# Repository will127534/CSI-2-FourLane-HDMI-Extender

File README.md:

# CSI-2-FourLane-HDMI-Extender
A simple MIPI CSI-2 extender with 4-lane support through HDMI cable

## Hardware
Technically, this isn’t supposed to work, but it kind of does. It relies on HDMI cables with Ethernet support to provide the fifth differential pair needed to transmit 4-lane MIPI signals through the HDMI cable.

The board is very simple. The receiver can either use the 3.3V from the FPC cable or an external power input to supply the HDMI connector’s power output. The HDMI connector location matches the USB connector on the Raspberry Pi 5 to simplify case design.

The transmitter board has a DC-DC step-down converter with a 3.3V output and a bypass option to power camera boards. For the StarlightEye (which needs a 5V input), there is also a connector that taps into the HDMI power input to supply power—this could also power something else, like an LED light source. Additionally, there is a QWIIC connector for sideband communication. Finally, the board’s form factor includes a cutout for the OneInchEye 2.0.

## Notes

This project came about because GMSL2 was too difficult to implement, and I needed something to extend my 4-lane MIPI cameras. If you’re reading this, you probably already know there are a few HDMI extender boards for MIPI cameras out there. However, most only support 2-lane MIPI, while I specifically needed 4-lane MIPI.

Where’s the catch? The standard HDMI cable only has four high-speed differential pairs, so that’s typically not enough for 4-lane MIPI (which requires 4 data pairs + 1 clock pair). However, HDMI includes an extension standard that reuses the HPD and UTILITY pins on the connector for a fifth differential pair called HEAC. This pair is meant for a bi-directional higher-speed sideband signal for Ethernet or Audio. Spec-wise, it doesn't have to carry signals as high-speed as the main video data. However, from a manufacturing standpoint, it’s often just as capable, because many manufacturers use the same type of differential pair cable for the fifth pair. (See [this teardown video by ChargerLab ](https://www.youtube.com/watch?v=UTeQvG3jk0k) as an example.)

For testing, I used the Cable Matters 2-Pack Ultra Thin HDMI Cable series; the 6-ft version is the maximum length that can run both the OneInchEye and StarlightEye at 1440 Mbps/lane with 4-lane MIPI.

Note: If you are using my IMX585 driver, you must lower the link speed from 1782 Mbps/lane to 1440 Mbps/lane by changing [this](https://github.com/will127534/imx585-v4l2-driver/blob/main/imx585.c#L210) line to 0x03.

Lastly, I did try using MIPI redrivers and retimers from [Ti](https://www.ti.com/product/SN65DPHY440SS) and [Diodes](https://www.diodes.com/part/view/PI2MEQX2505). The receiver board was originally designed with an active redriver/retimer (both parts are conveniently pin-to-pin compatible). However, due to the board’s pin layout, the differential pairs would need a polarity swap, and TI’s retimer wouldn’t work, even with [this register](https://e2e.ti.com/support/interface-group/interface/f/interface-forum/1187578/sn65dphy440ss-in-a-csi-application-is-it-possible-to-invert-n-and-p-on-both-sides-of-the-chip-except-for-the-clk) configured. As for the redriver, for some reason I couldn’t get it to work well with a 6-ft cable—only with a very short HDMI cable. The redriver is polarity-invariant, but even after playing around with the different tuning options, it just didn’t seem to work reliably. Suggestions are welcome in the issues/comments section.

## Footnotes

* Gerber, BOM, and CPL files for JLCPCB are under /Gerber and /bom in each Transmitter and Receiver board folder.
* [Interactive BOM for Receiver](https://htmlpreview.github.io/?https://github.com/will127534/CSI-2-FourLane-HDMI-Extender/blob/main/Receiver/bom/ibom.html) [(provided by InteractiveHtmlBom)
](https://github.com/openscopeproject/InteractiveHtmlBom)
* [Interactive BOM for Transmitter](https://htmlpreview.github.io/?https://github.com/will127534/CSI-2-FourLane-HDMI-Extender/blob/main/Transmitter/bom/ibom.html) [(provided by InteractiveHtmlBom)
](https://github.com/openscopeproject/InteractiveHtmlBom)
* Yes It still supports 2-lane MIPI cameras (tested with the IMX708 Raspberry Pi Camera V3).
* I have almost no intention of selling this on Tindie, because I can already imagine users who don’t fully understand the details running into troubles and complaining about it.
* [@VoeGalore](https://github.com/VoeGalore/CSI-2-FourLane-HDMI-Extender) made 3D-printable cases for using the transmitter board with starlighteye(IMX585), oneincheye(IMX283), and Camera Module V3. STL files are under /case-STL in each folders. Additional hardware might be needed (M2x16 screws, M2x6 screws, M2 threaded insert, 1/4-20 threaded insert).

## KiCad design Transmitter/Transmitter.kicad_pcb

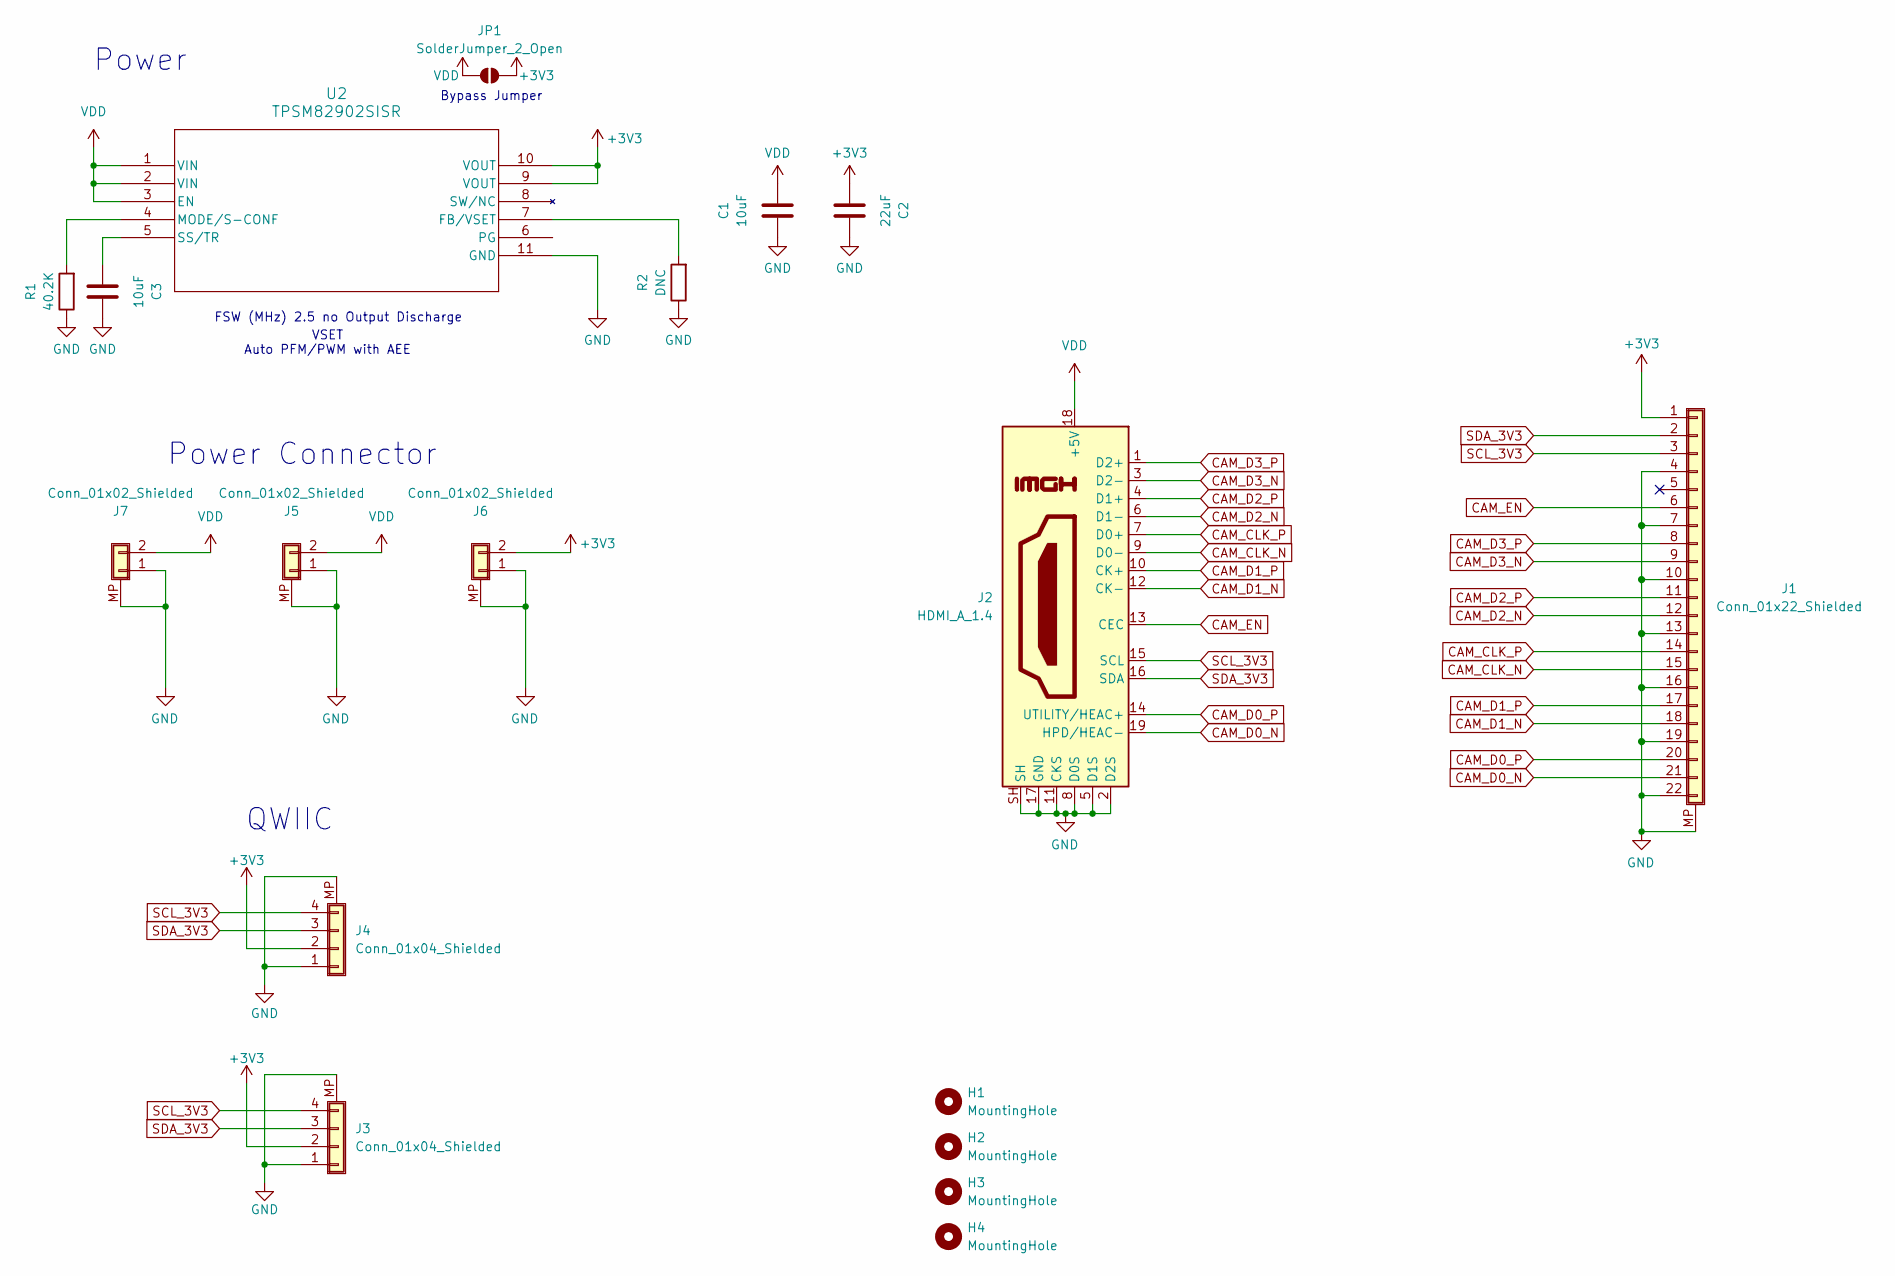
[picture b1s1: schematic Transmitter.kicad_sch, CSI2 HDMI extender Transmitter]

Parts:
C1: 10uF; C_0805_2012Metric
C2: 22uF; C_0805_2012Metric
C3: 10uF; C_0402_1005Metric
H1, H2, H3, H4: MountingHole; MountingHole_2.2mm_M2
J1: Conn_01x22_Shielded; Hirose_FH12-22S-0.5SH_1x22-1MP_P0.50mm_Horizontal
J2: HDMI_A_1.4; HDMI_A_Molex_208658-1001_Horizontal
J3, J4: Conn_01x04_Shielded; JST_SH_SM04B-SRSS-TB_1x04-1MP_P1.00mm_Horizontal
J5, J6, J7: Conn_01x02_Shielded; Molex_PicoBlade_53398-0271_1x02-1MP_P1.25mm_Vertical
JP1: SolderJumper_2_Open; SolderJumper-2_P1.3mm_Open_RoundedPad1.0x1.5mm
R1: 40.2K; R_0402_1005Metric
R2: DNC; R_0402_1005Metric
U2: TPSM82902SISR; uSIP11_SIS_TEX

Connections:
+3V3: C2.1, J1.1, J3.2, J4.2, J6.2, JP1.2 (B), U2.9 (VOUT), U2.10 (VOUT)
CAM_CLK_N: J1.15, J2.9 (D0-)
CAM_CLK_P: J1.14, J2.7 (D0+)
CAM_D0_N: J1.21, J2.19 (HPD/HEAC-)
CAM_D0_P: J1.20, J2.14 (UTILITY/HEAC+)
CAM_D1_N: J1.18, J2.12 (CK-)
CAM_D1_P: J1.17, J2.10 (CK+)
CAM_D2_N: J1.12, J2.6 (D1-)
CAM_D2_P: J1.11, J2.4 (D1+)
CAM_D3_N: J1.9, J2.3 (D2-)
CAM_D3_P: J1.8, J2.1 (D2+)
CAM_EN: J1.6, J2.13 (CEC)
GND: C1.1, C2.2, C3.2, J1.4, J1.7, J1.10, J1.13, J1.16, J1.19, J1.22, J1.MP (Shield), J2.2 (D2S), J2.5 (D1S), J2.8 (D0S), J2.11 (CKS), J2.17 (GND), J2.SH, J3.1, J3.MP (Shield), J4.1, J4.MP (Shield), J5.1, J5.MP (Shield), J6.1, J6.MP (Shield), J7.1, J7.MP (Shield), R1.1, R2.1, U2.11 (GND)
unnamed: R2.2, U2.7 (FB/VSET)
unnamed: R1.2, U2.4 (MODE/S-CONF)
unnamed: C3.1, U2.5 (SS/TR)
SCL_3V3: J1.3, J2.15 (SCL), J3.4, J4.4
SDA_3V3: J1.2, J2.16 (SDA), J3.3, J4.3
VDD: C1.2, J2.18 (+5V), J5.2, J7.2, JP1.1 (A), U2.1 (VIN), U2.2 (VIN), U2.3 (EN)

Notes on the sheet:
Power Connector
FSW (MHz) 2.5 no Output Discharge
Power
VSET Auto PFM/PWM with AEE
QWIIC
Bypass Jumper

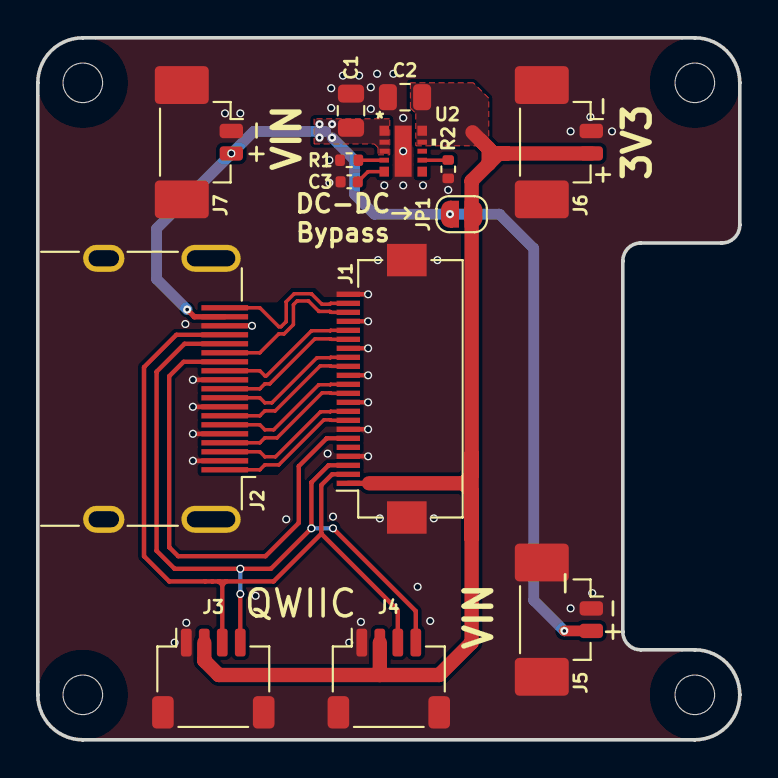
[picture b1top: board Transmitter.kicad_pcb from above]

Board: 2 copper layers, 39.0 x 39.0 mm, 18 parts (0 on the bottom side), 19 nets.

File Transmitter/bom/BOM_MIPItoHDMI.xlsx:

Comment | Designator | Footprint | JLCPCB Part #（optional）
Conn_01x02_Shielded | J7,J6,J5 | Molex_PicoBlade_53398-0271_1x02-1MP_P1.25mm_Vertical | C122410
Conn_01x04_Shielded | J4,J3 | JST_SH_SM04B-SRSS-TB_1x04-1MP_P1.00mm_Horizontal | C160404
TPSM82902SISR | U2 | uSIP11_SIS_TEX | C6339351
Conn_01x22_Shielded | J1 | Hirose_FH12-22S-0.5SH_1x22-1MP_P0.50mm_Horizontal | C597981
40.2K | R1 | R_0402_1005Metric
22uF | C2 | C_0805_2012Metric
10uF | C3 | C_0402_1005Metric
10uF | C1 | C_0805_2012Metric
HDMI_A_1.4 | J2 | HDMI_A_Molex_208658-1001_Horizontal | C111617

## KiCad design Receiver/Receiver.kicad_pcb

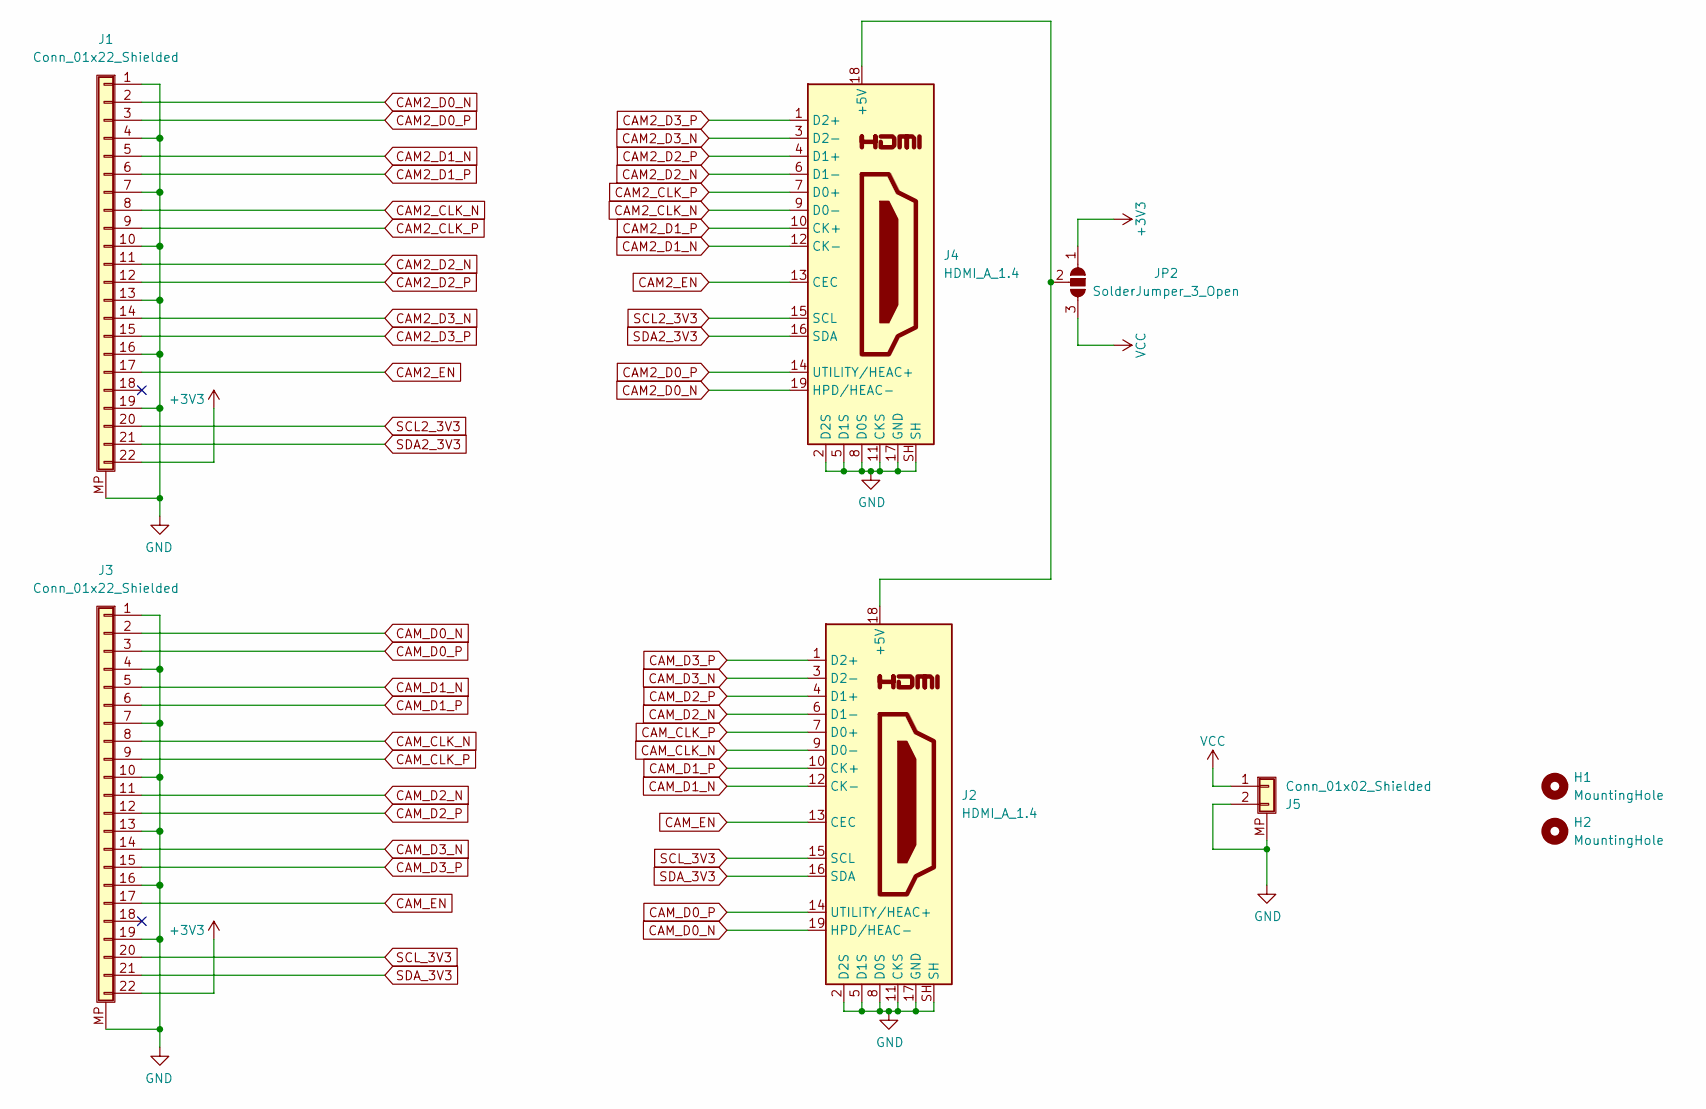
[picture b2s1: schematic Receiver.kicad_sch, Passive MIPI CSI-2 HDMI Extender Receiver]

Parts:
H1, H2: MountingHole; MountingHole_2.7mm_M2.5
J1, J3: Conn_01x22_Shielded; TF3822S05SV830
J2, J4: HDMI_A_1.4; HDMI_A_Molex_208658-1001_Horizontal
J5: Conn_01x02_Shielded; Molex_PicoBlade_53261-0271_1x02-1MP_P1.25mm_Horizontal
JP2: SolderJumper_3_Open; SolderJumper-3_P1.3mm_Open_RoundedPad1.0x1.5mm_NumberLabels

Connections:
+3V3: J1.22, J3.22, JP2.1 (A)
CAM2_CLK_N: J1.8, J4.9 (D0-)
CAM2_CLK_P: J1.9, J4.7 (D0+)
CAM2_D0_N: J1.2, J4.19 (HPD/HEAC-)
CAM2_D0_P: J1.3, J4.14 (UTILITY/HEAC+)
CAM2_D1_N: J1.5, J4.12 (CK-)
CAM2_D1_P: J1.6, J4.10 (CK+)
CAM2_D2_N: J1.11, J4.6 (D1-)
CAM2_D2_P: J1.12, J4.4 (D1+)
CAM2_D3_N: J1.14, J4.3 (D2-)
CAM2_D3_P: J1.15, J4.1 (D2+)
CAM2_EN: J1.17, J4.13 (CEC)
CAM_CLK_N: J2.9 (D0-), J3.8
CAM_CLK_P: J2.7 (D0+), J3.9
CAM_D0_N: J2.19 (HPD/HEAC-), J3.2
CAM_D0_P: J2.14 (UTILITY/HEAC+), J3.3
CAM_D1_N: J2.12 (CK-), J3.5
CAM_D1_P: J2.10 (CK+), J3.6
CAM_D2_N: J2.6 (D1-), J3.11
CAM_D2_P: J2.4 (D1+), J3.12
CAM_D3_N: J2.3 (D2-), J3.14
CAM_D3_P: J2.1 (D2+), J3.15
CAM_EN: J2.13 (CEC), J3.17
GND: J1.1, J1.4, J1.7, J1.10, J1.13, J1.16, J1.19, J1.MP (Shield), J2.2 (D2S), J2.5 (D1S), J2.8 (D0S), J2.11 (CKS), J2.17 (GND), J2.SH, J3.1, J3.4, J3.7, J3.10, J3.13, J3.16, J3.19, J3.MP (Shield), J4.2 (D2S), J4.5 (D1S), J4.8 (D0S), J4.11 (CKS), J4.17 (GND), J4.SH, J5.2, J5.MP (Shield)
unnamed: J2.18 (+5V), J4.18 (+5V), JP2.2 (C)
SCL2_3V3: J1.20, J4.15 (SCL)
SCL_3V3: J2.15 (SCL), J3.20
SDA2_3V3: J1.21, J4.16 (SDA)
SDA_3V3: J2.16 (SDA), J3.21
VCC: J5.1, JP2.3 (B)

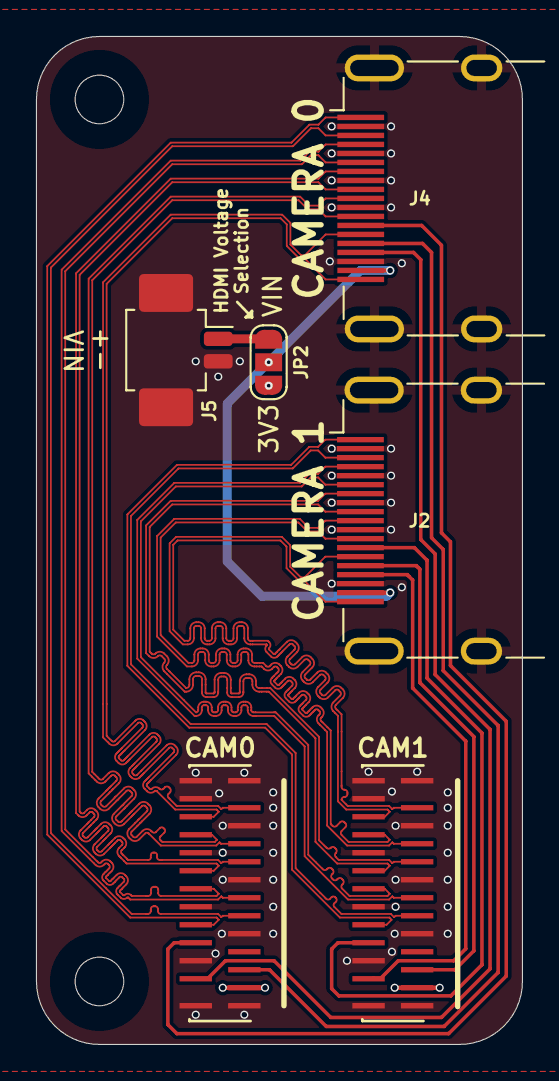
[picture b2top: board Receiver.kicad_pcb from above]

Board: 4 copper layers, 27.0 x 56.0 mm, 8 parts (0 on the bottom side), 30 nets.

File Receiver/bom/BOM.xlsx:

Comment | Designator | Footprint | JLCPCB Part #（optional）
HDMI-019S | J4,J2 | HDMI_A_Molex_208658-1001_Horizontal | C111617
Conn_01x22_Shielded | J1,J3 | TF3822S05SV830 | C6552695
Conn_01x02_Shielded | J5 | Molex_PicoBlade_53261-0271_1x02-1MP_P1.25mm_Horizontal | C177225

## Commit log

2025-03-02 Init
2025-03-02 Update Filename
2025-03-02 Update README.md image link
2025-03-03 Add photos of 3D-printed cases
2025-03-03 Add STL files of 3D printed cases
2025-03-03 added 3D printed case in footnote
2025-03-03 Add files for 3D printed cases
2025-03-03 Update README.md - showing image for the case
2025-03-03 update the image real quick
